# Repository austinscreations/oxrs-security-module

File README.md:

# oxrs-security-module
module 8 port pcb that allows for EOL monitoring of security sensors

2023-10-25 version 210 was created to fix p fet issue also updated JLCPCB PCBa files for the modular I2CRJ45 and port PWR extention

this baord is a 4 layer board

port PWR is 2 layers

port PWR extention is a remote switch that allows you to turn ports on and off. the use of a 1.25mm jst cable could eb used instead, simply with pin 5 being GND connect the others to this and a port will be ON

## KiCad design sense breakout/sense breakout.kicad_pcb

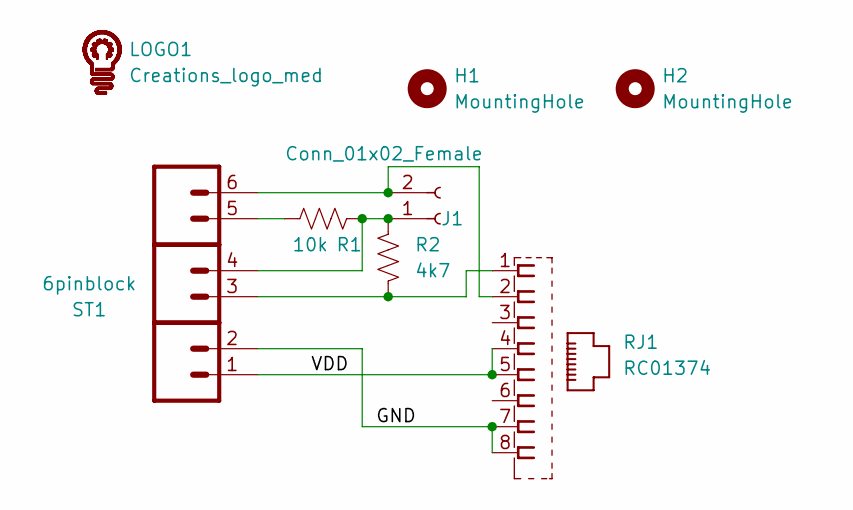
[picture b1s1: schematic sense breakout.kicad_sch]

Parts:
H1, H2: MountingHole; MountingHole_3.2mm_M3
J1: Conn_01x02_Female; PinHeader_1x02_P2.54mm_Vertical; LCSC C2829889
LOGO1: Creations_logo_med; Creations logo med
R1: 10k; R_0603_1608Metric; LCSC C25804
R2: 4k7; R_0603_1608Metric; LCSC C23162
RJ1: RC01374; LCSC C385834
ST1: 6pinblock; LCSC C192781

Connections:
/GND: RJ1.7, RJ1.8, ST1.2
/VDD: RJ1.4, RJ1.5, ST1.1
unnamed: J1.1, R1.1, R2.1, ST1.4
unnamed: J1.2, RJ1.2, ST1.6
unnamed: R1.2, ST1.5
unnamed: R2.2, RJ1.1, ST1.3

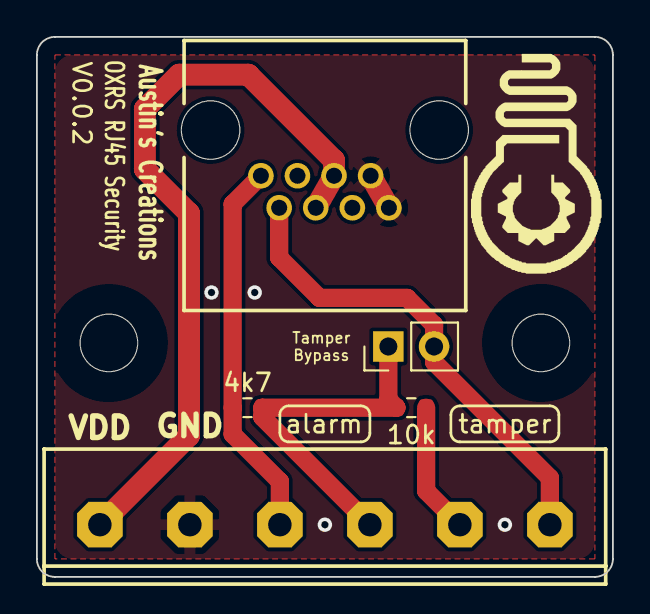
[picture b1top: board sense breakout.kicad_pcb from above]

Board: 2 copper layers, 32.0 x 30.0 mm, 8 parts (0 on the bottom side), 6 nets.

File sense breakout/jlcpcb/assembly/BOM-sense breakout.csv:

Comment,Designator,Footprint,LCSC
6pinblock,ST1,6pinblock,C192781
4k7,R2,R_0603_1608Metric,C23162
10k,R1,R_0603_1608Metric,C25804
Conn_01x02_Female,J1,PinHeader_1x02_P2.54mm_Vertical,C2829889
RC01374,RJ1,RC01374,C385834

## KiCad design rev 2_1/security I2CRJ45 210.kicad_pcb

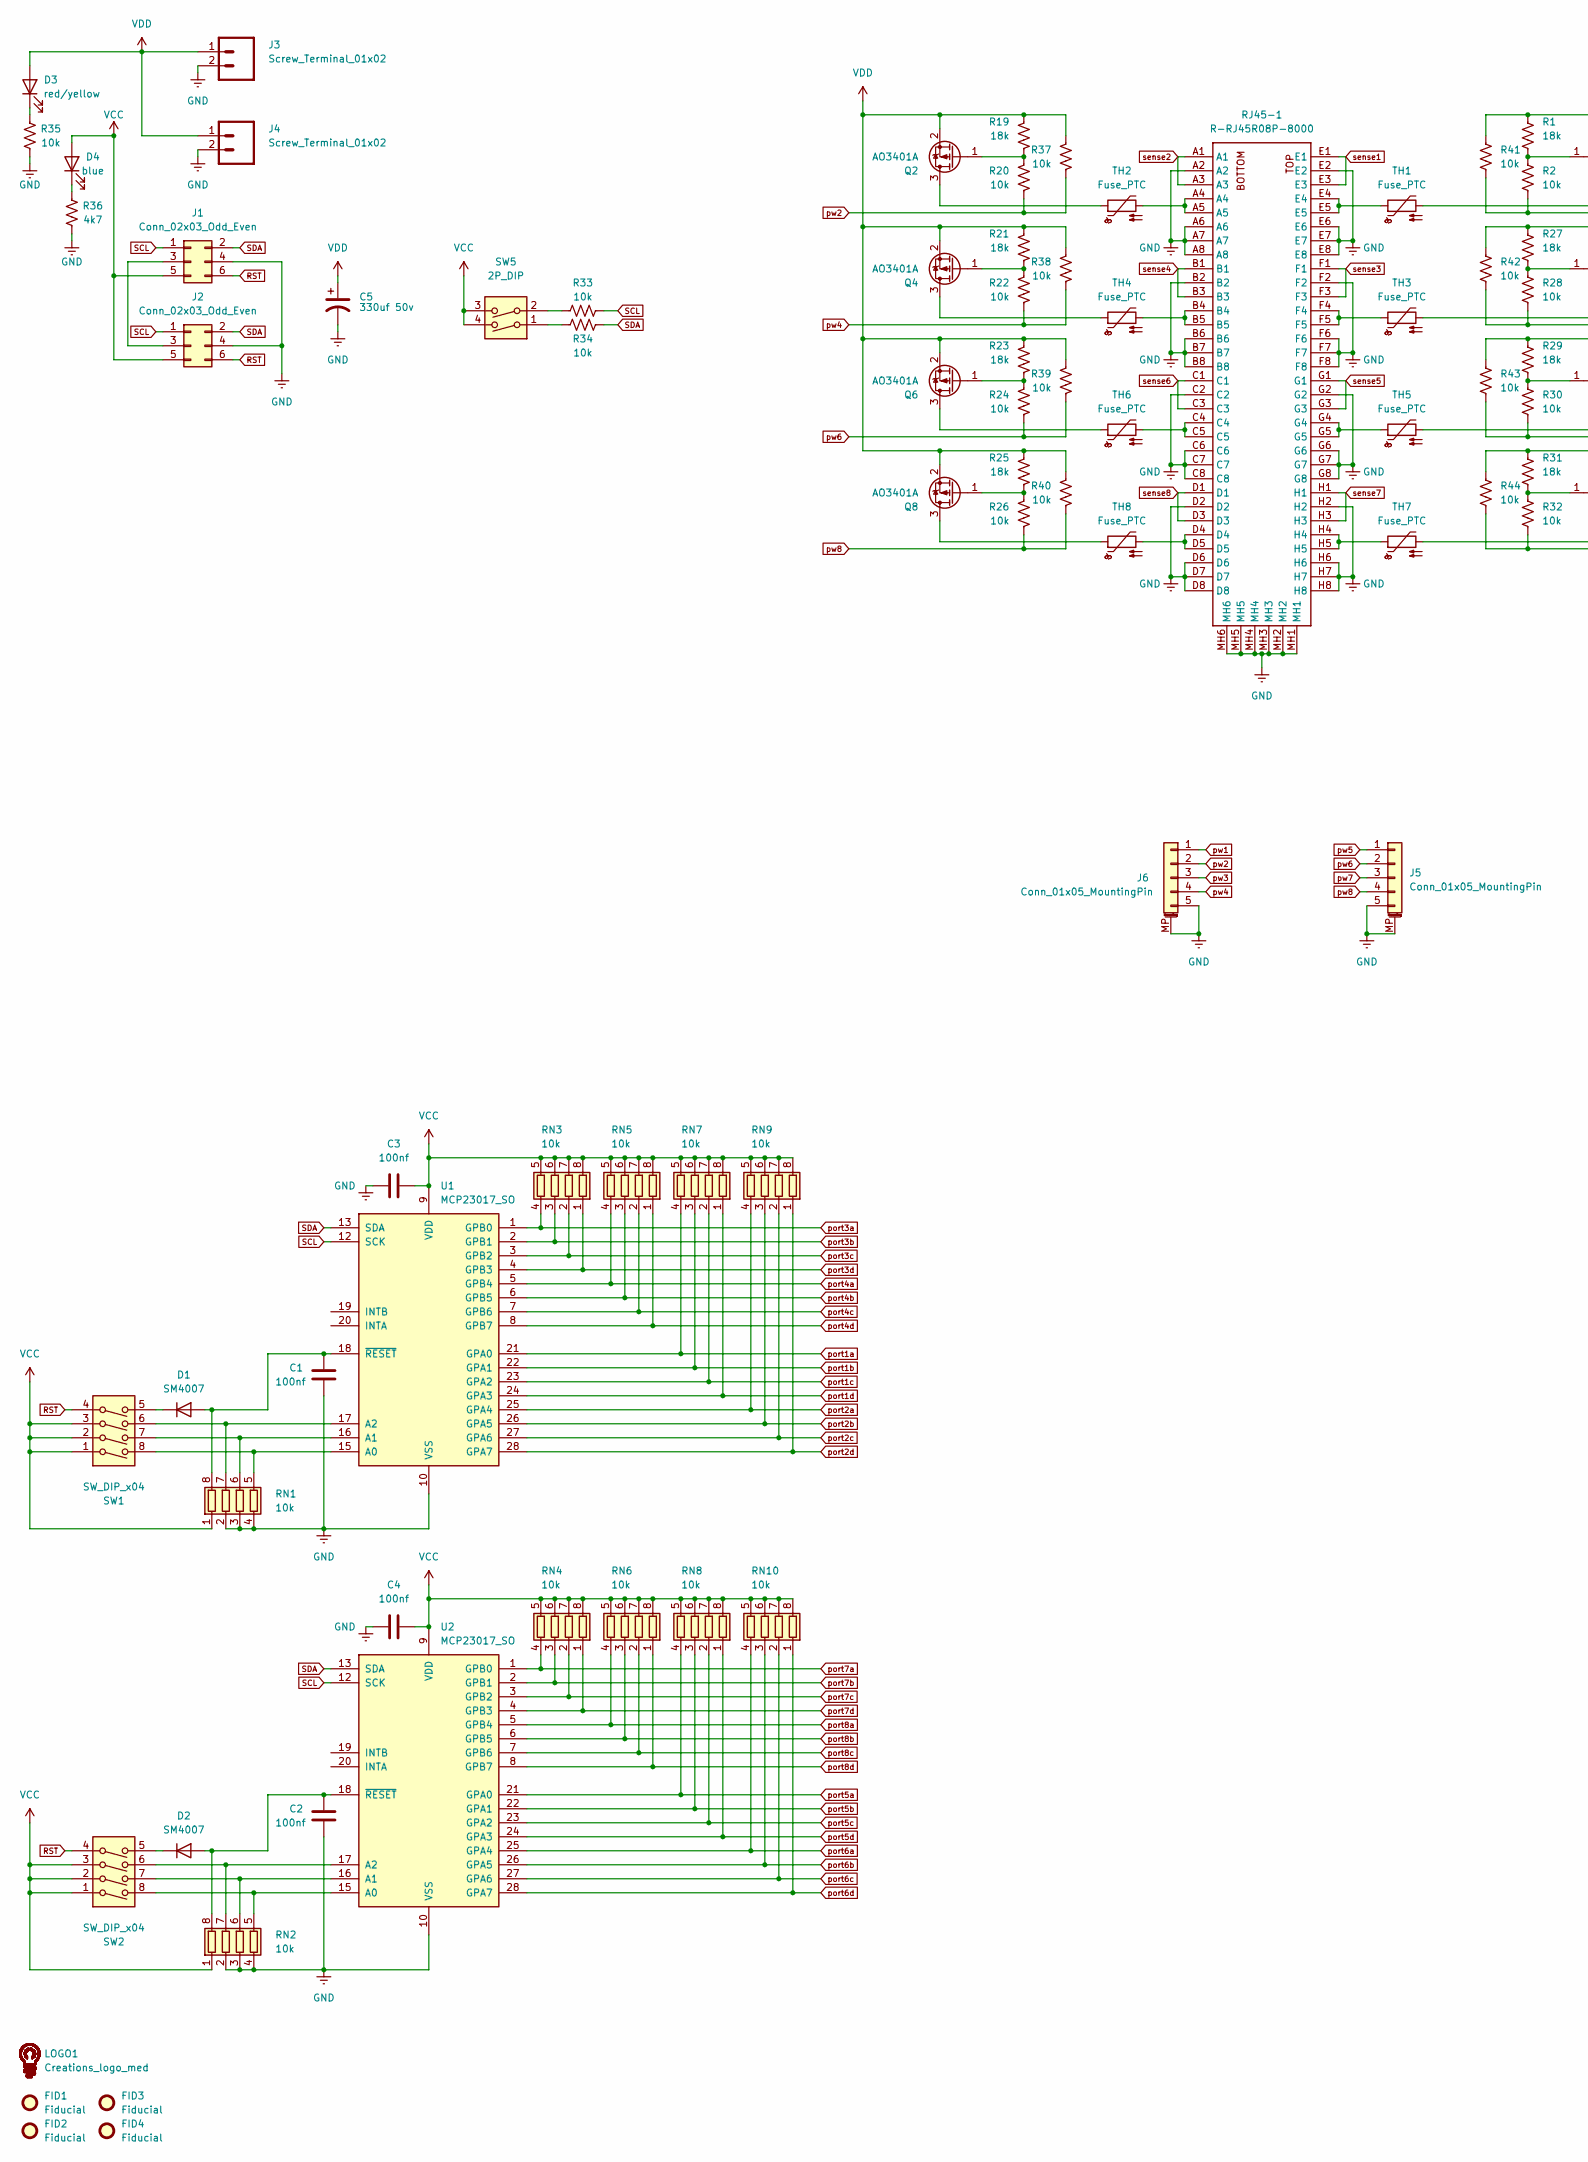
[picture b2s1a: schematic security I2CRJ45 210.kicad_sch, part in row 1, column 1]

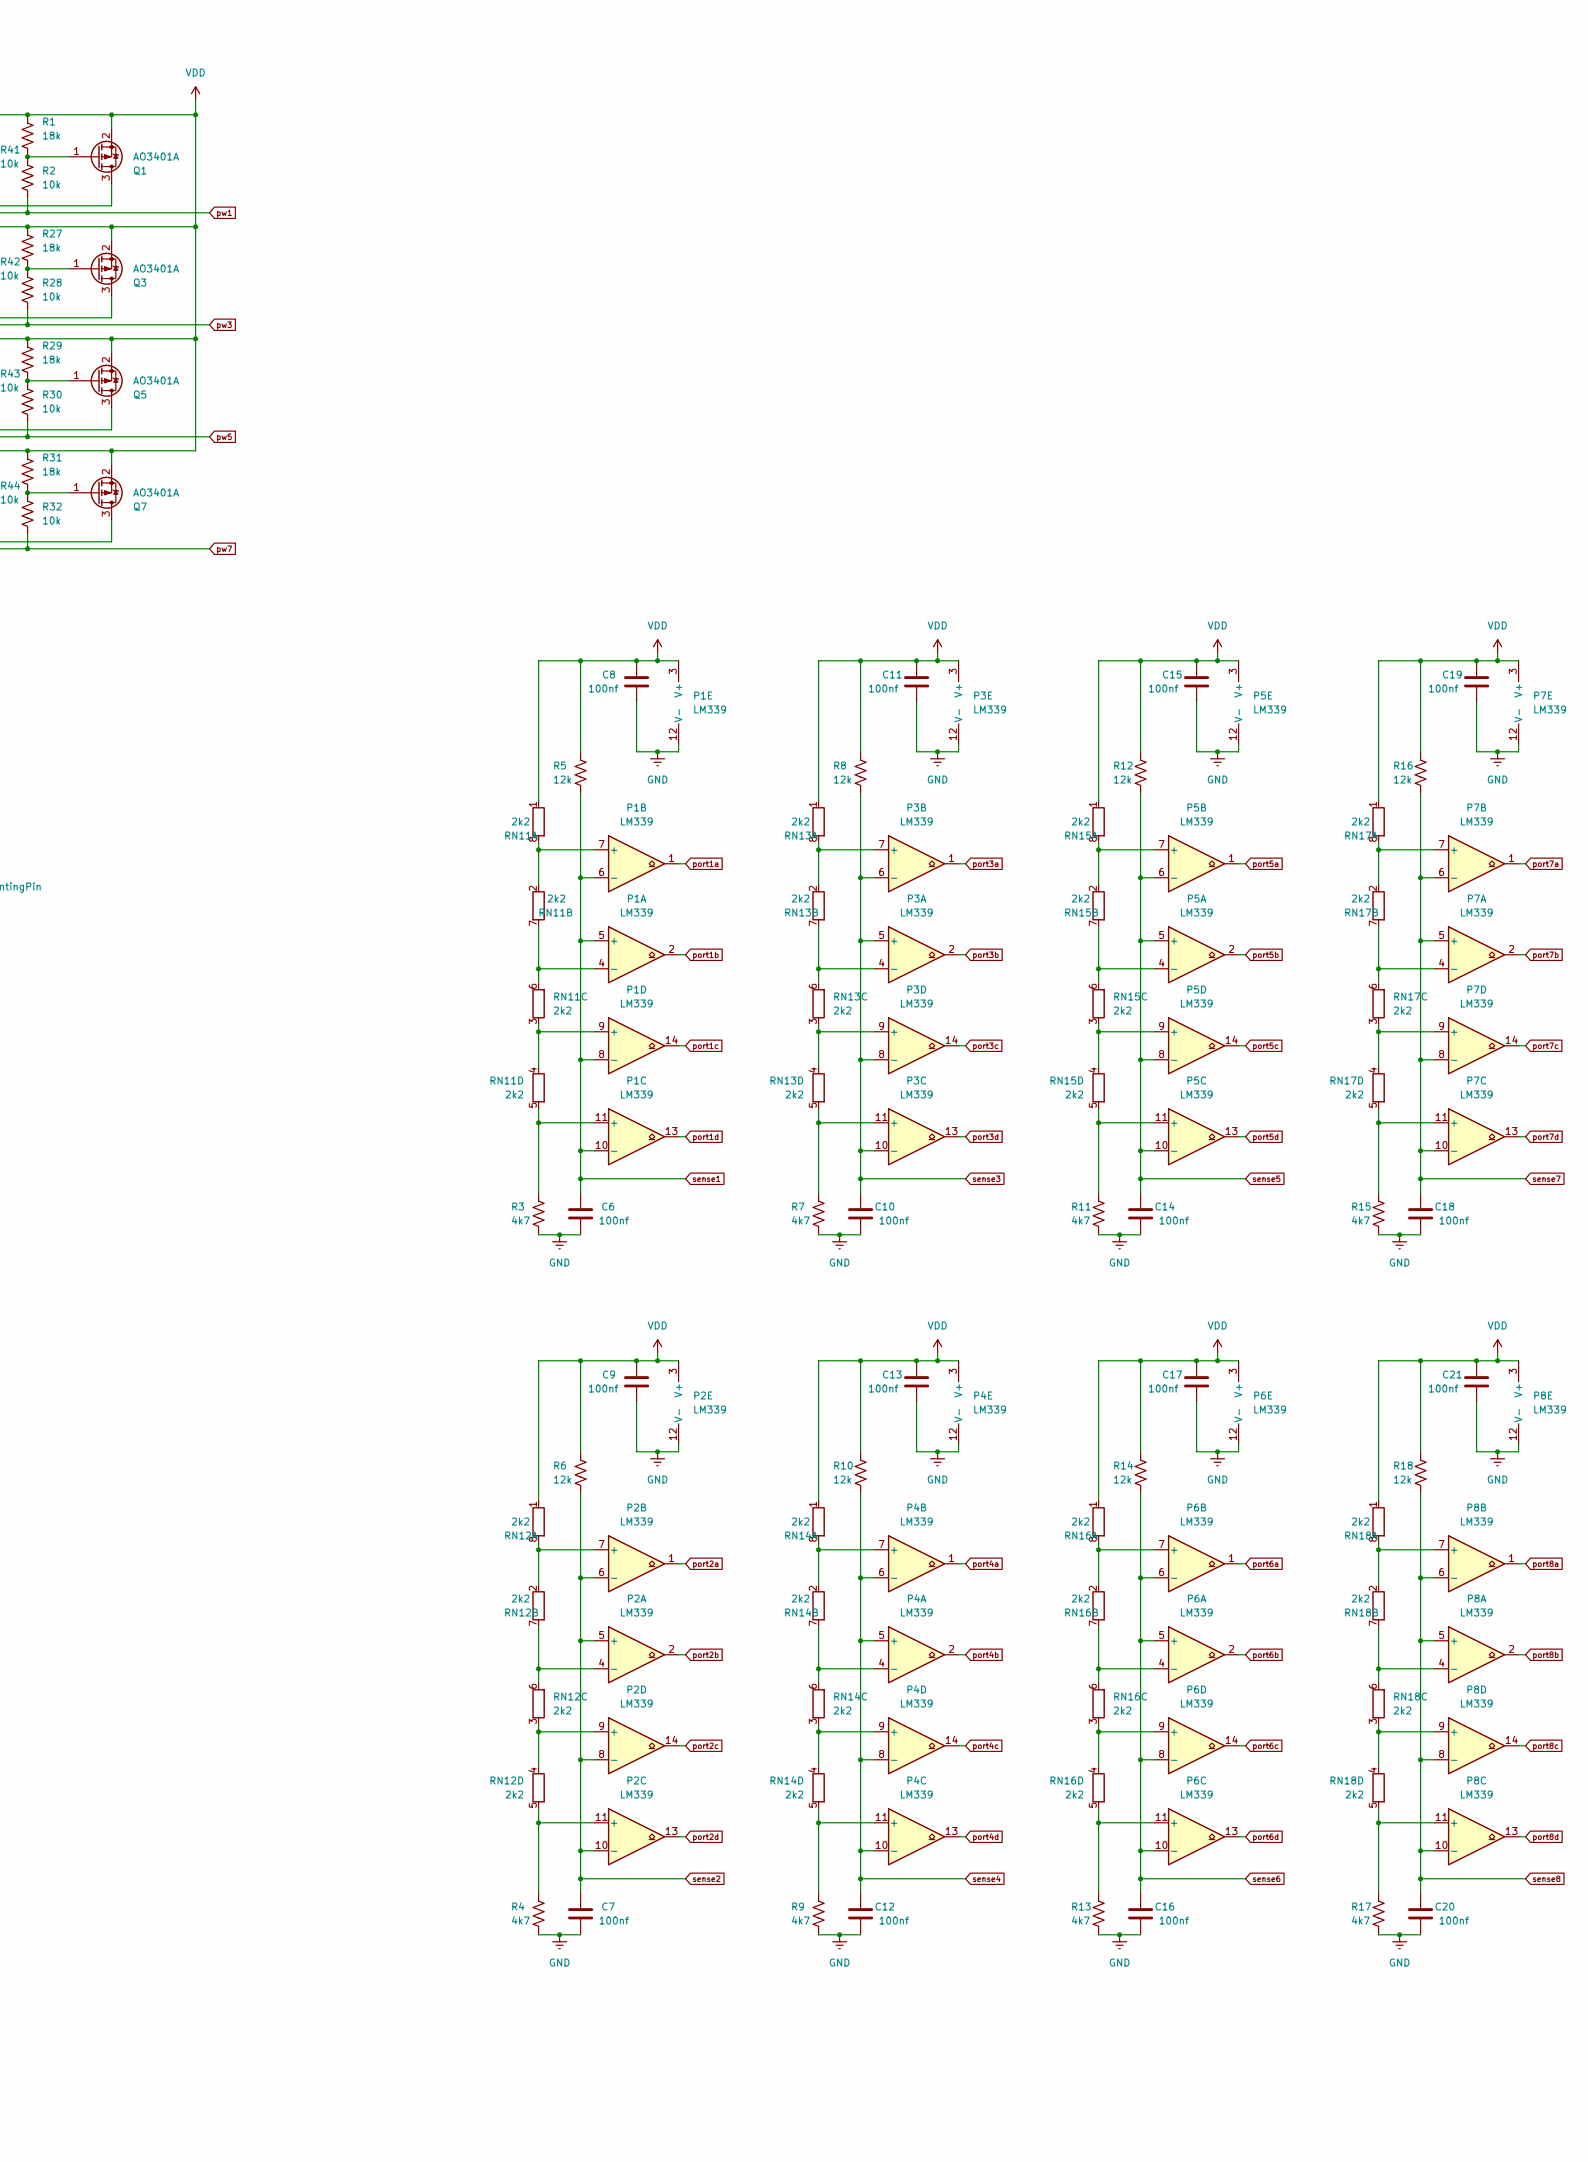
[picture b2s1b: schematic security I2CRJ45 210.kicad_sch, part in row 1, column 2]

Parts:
C1, C2, C3, C4, C6, C7, C8, C9, C10, C11, C12, C13, C14, C15, C16, C17, C18, C19, C20, C21: 100nf; C_0603_1608Metric; LCSC C14663
C5: 330uf 50v; CP_Elec_10x10; LCSC C2895745
D1, D2: SM4007; D_SOD-123F; LCSC C64898
D3: red/yellow; LED_0603_1608Metric; LCSC C72038
D4: blue; LED_0603_1608Metric; LCSC C72041
FID1, FID2, FID3, FID4: Fiducial; Fiducial_1mm_Mask2mm
J1, J2: Conn_02x03_Odd_Even; IDC-Header_2x03_P2.54mm_Vertical; LCSC C132438
J3, J4: Screw_Terminal_01x02; 2pinblock; LCSC C3703
J5, J6: Conn_01x05_MountingPin; JST_GH_SM05B-GHS-TB_1x05-1MP_P1.25mm_Horizontal; LCSC C225114
LOGO1: Creations_logo_med; Creations logo med
P1, P2, P3, P4, P5, P6, P7, P8: LM339; TSSOP-14_4.4x5mm_P0.65mm; part # 511-LM339DT; LCSC C42184
Q1, Q2, Q3, Q4, Q5, Q6, Q7, Q8: AO3401A; SOT-23; LCSC C15127
R1, R19, R21, R23, R25, R27, R29, R31: 18k; R_0603_1608Metric; LCSC C25810
R2, R20, R22, R24, R26, R28, R30, R32, R33, R34, R35, R37, R38, R39, R40, R41, R42, R43, R44: 10k; R_0603_1608Metric; LCSC C25804
R3, R4, R7, R9, R11, R13, R15, R17, R36: 4k7; R_0603_1608Metric; LCSC C21190
R5, R6, R8, R10, R12, R14, R16, R18: 12k; R_0603_1608Metric; LCSC C22790
RJ45-1: R-RJ45R08P-8000; LCSC C386760
RN1, RN2, RN3, RN4, RN5, RN6, RN7, RN8, RN9, RN10: 10k; R_Array_Convex_4x0603; LCSC C29718
RN11, RN12, RN13, RN14, RN15, RN16, RN17, RN18: 2k2; R_Array_Convex_4x0603; LCSC C12001
SW1, SW2: SW_DIP_x04; 4P_DIP; LCSC C2758183
SW5: 2P_DIP; LCSC C2758181
TH1, TH2, TH3, TH4, TH5, TH6, TH7, TH8: Fuse_PTC; R_0603_1608Metric; LCSC C883087
U1, U2: MCP23017_SO; SOIC-28W_7.5x17.9mm_P1.27mm; LCSC C47023

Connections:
GNDREF: C1.2, C2.2, C3.1, C4.1, C5.2, C6.2, C7.2, C8.2, C9.2, C10.2, C11.2, C12.2, C13.2, C14.2, C15.2, C16.2, C17.2, C18.2, C19.2, C20.2, C21.2, J1.4, J2.4, J3.2, J4.2, J5.5, J5.MP (MountPin), J6.5, J6.MP (MountPin), P1.12 (V-), P2.12 (V-), P3.12 (V-), P4.12 (V-), P5.12 (V-), P6.12 (V-), P7.12 (V-), P8.12 (V-), R3.2, R4.2, R7.2, R9.2, R11.2, R13.2, R15.2, R17.2, R35.2, R36.2, RJ45-1.A2, RJ45-1.A6, RJ45-1.A7, RJ45-1.A8, RJ45-1.B2, RJ45-1.B6, RJ45-1.B7, RJ45-1.B8, RJ45-1.C2, RJ45-1.C6, RJ45-1.C7, RJ45-1.C8, RJ45-1.D2, RJ45-1.D6, RJ45-1.D7, RJ45-1.D8, RJ45-1.E2, RJ45-1.E6, RJ45-1.E7, RJ45-1.E8, RJ45-1.F2, RJ45-1.F6, RJ45-1.F7, RJ45-1.F8, RJ45-1.G2, RJ45-1.G6, RJ45-1.G7, RJ45-1.G8, RJ45-1.H2, RJ45-1.H6, RJ45-1.H7, RJ45-1.H8, RJ45-1.MH1, RJ45-1.MH2, RJ45-1.MH3, RJ45-1.MH4, RJ45-1.MH5, RJ45-1.MH6, RN1.2 (R2.1), RN1.3 (R3.1), RN1.4 (R4.1), RN2.2 (R2.1), RN2.3 (R3.1), RN2.4 (R4.1), U1.10 (VSS), U2.10 (VSS)
unnamed: C1.1, D1.2 (A), RN1.8 (R1.2), U1.18 (~RESET)
unnamed: C2.1, D2.2 (A), RN2.8 (R1.2), U2.18 (~RESET)
unnamed: D1.1 (K), SW1.5
unnamed: D2.1 (K), SW2.5
unnamed: D3.1 (K), R35.1
unnamed: D4.1 (K), R36.1
unnamed: J1.3, J2.3
unnamed: P1.4 (-), RN11.6 (R3.2), RN11.7 (R2.2)
unnamed: P1.7 (+), RN11.2 (R2.1), RN11.8 (R1.2)
unnamed: P1.9 (+), RN11.3 (R3.1), RN11.4 (R4.1)
unnamed: P1.11 (+), R3.1, RN11.5 (R4.2)
unnamed: P2.4 (-), RN12.6 (R3.2), RN12.7 (R2.2)
unnamed: P2.7 (+), RN12.2 (R2.1), RN12.8 (R1.2)
unnamed: P2.9 (+), RN12.3 (R3.1), RN12.4 (R4.1)
unnamed: P2.11 (+), R4.1, RN12.5 (R4.2)
unnamed: P3.4 (-), RN13.6 (R3.2), RN13.7 (R2.2)
unnamed: P3.7 (+), RN13.2 (R2.1), RN13.8 (R1.2)
unnamed: P3.9 (+), RN13.3 (R3.1), RN13.4 (R4.1)
unnamed: P3.11 (+), R7.1, RN13.5 (R4.2)
unnamed: P4.4 (-), RN14.6 (R3.2), RN14.7 (R2.2)
unnamed: P4.7 (+), RN14.2 (R2.1), RN14.8 (R1.2)
unnamed: P4.9 (+), RN14.3 (R3.1), RN14.4 (R4.1)
unnamed: P4.11 (+), R9.1, RN14.5 (R4.2)
unnamed: P5.4 (-), RN15.6 (R3.2), RN15.7 (R2.2)
unnamed: P5.7 (+), RN15.2 (R2.1), RN15.8 (R1.2)
unnamed: P5.9 (+), RN15.3 (R3.1), RN15.4 (R4.1)
unnamed: P5.11 (+), R11.1, RN15.5 (R4.2)
unnamed: P6.4 (-), RN16.6 (R3.2), RN16.7 (R2.2)
unnamed: P6.7 (+), RN16.2 (R2.1), RN16.8 (R1.2)
unnamed: P6.9 (+), RN16.3 (R3.1), RN16.4 (R4.1)
unnamed: P6.11 (+), R13.1, RN16.5 (R4.2)
unnamed: P7.4 (-), RN17.6 (R3.2), RN17.7 (R2.2)
unnamed: P7.7 (+), RN17.2 (R2.1), RN17.8 (R1.2)
unnamed: P7.9 (+), RN17.3 (R3.1), RN17.4 (R4.1)
unnamed: P7.11 (+), R15.1, RN17.5 (R4.2)
unnamed: P8.4 (-), RN18.6 (R3.2), RN18.7 (R2.2)
unnamed: P8.7 (+), RN18.2 (R2.1), RN18.8 (R1.2)
unnamed: P8.9 (+), RN18.3 (R3.1), RN18.4 (R4.1)
unnamed: P8.11 (+), R17.1, RN18.5 (R4.2)
unnamed: Q1.1 (G), R1.2, R2.1
unnamed: Q1.3 (D), TH1.2
unnamed: Q2.1 (G), R19.2, R20.1
unnamed: Q2.3 (D), TH2.1
unnamed: Q3.1 (G), R27.2, R28.1
unnamed: Q3.3 (D), TH3.2
unnamed: Q4.1 (G), R21.2, R22.1
unnamed: Q4.3 (D), TH4.1
unnamed: Q5.1 (G), R29.2, R30.1
unnamed: Q5.3 (D), TH5.2
unnamed: Q6.1 (G), R23.2, R24.1
unnamed: Q6.3 (D), TH6.1
unnamed: Q7.1 (G), R31.2, R32.1
unnamed: Q7.3 (D), TH7.2
unnamed: Q8.1 (G), R25.2, R26.1
unnamed: Q8.3 (D), TH8.1
unnamed: R33.1, SW5.2
unnamed: R34.1, SW5.1
unnamed: RJ45-1.A4, RJ45-1.A5, TH2.2
unnamed: RJ45-1.B4, RJ45-1.B5, TH4.2
unnamed: RJ45-1.C4, RJ45-1.C5, TH6.2
unnamed: RJ45-1.D4, RJ45-1.D5, TH8.2
unnamed: RJ45-1.E4, RJ45-1.E5, TH1.1
unnamed: RJ45-1.F4, RJ45-1.F5, TH3.1
unnamed: RJ45-1.G4, RJ45-1.G5, TH5.1
unnamed: RJ45-1.H4, RJ45-1.H5, TH7.1
unnamed: RN1.5 (R4.2), SW1.8, U1.15 (A0)
unnamed: RN1.6 (R3.2), SW1.7, U1.16 (A1)
unnamed: RN1.7 (R2.2), SW1.6, U1.17 (A2)
unnamed: RN2.5 (R4.2), SW2.8, U2.15 (A0)
unnamed: RN2.6 (R3.2), SW2.7, U2.16 (A1)
unnamed: RN2.7 (R2.2), SW2.6, U2.17 (A2)
RST: J1.6, J2.6, SW1.4, SW2.4
SCL: J1.1, J2.1, R33.2, U1.12 (SCK), U2.12 (SCK)
SDA: J1.2, J2.2, R34.2, U1.13 (SDA), U2.13 (SDA)
VCC: C3.2, C4.2, D4.2 (A), J1.5, J2.5, RN1.1 (R1.1), RN2.1 (R1.1), RN3.5 (R4.2), RN3.6 (R3.2), RN3.7 (R2.2), RN3.8 (R1.2), RN4.5 (R4.2), RN4.6 (R3.2), RN4.7 (R2.2), RN4.8 (R1.2), RN5.5 (R4.2), RN5.6 (R3.2), RN5.7 (R2.2), RN5.8 (R1.2), RN6.5 (R4.2), RN6.6 (R3.2), RN6.7 (R2.2), RN6.8 (R1.2), RN7.5 (R4.2), RN7.6 (R3.2), RN7.7 (R2.2), RN7.8 (R1.2), RN8.5 (R4.2), RN8.6 (R3.2), RN8.7 (R2.2), RN8.8 (R1.2), RN9.5 (R4.2), RN9.6 (R3.2), RN9.7 (R2.2), RN9.8 (R1.2), RN10.5 (R4.2), RN10.6 (R3.2), RN10.7 (R2.2), RN10.8 (R1.2), SW1.1, SW1.2, SW1.3, SW2.1, SW2.2, SW2.3, SW5.3, SW5.4, U1.9 (VDD), U2.9 (VDD)
VDD: C5.1, C8.1, C9.1, C11.1, C13.1, C15.1, C17.1, C19.1, C21.1, D3.2 (A), J3.1, J4.1, P1.3 (V+), P2.3 (V+), P3.3 (V+), P4.3 (V+), P5.3 (V+), P6.3 (V+), P7.3 (V+), P8.3 (V+), Q1.2 (S), Q2.2 (S), Q3.2 (S), Q4.2 (S), Q5.2 (S), Q6.2 (S), Q7.2 (S), Q8.2 (S), R1.1, R5.1, R6.1, R8.1, R10.1, R12.1, R14.1, R16.1, R18.1, R19.1, R21.1, R23.1, R25.1, R27.1, R29.1, R31.1, R37.1, R38.1, R39.1, R40.1, R41.1, R42.1, R43.1, R44.1, RN11.1 (R1.1), RN12.1 (R1.1), RN13.1 (R1.1), RN14.1 (R1.1), RN15.1 (R1.1), RN16.1 (R1.1), RN17.1 (R1.1), RN18.1 (R1.1)
port1a: P1.1, RN7.4 (R4.1), U1.21 (GPA0)
port1b: P1.2, RN7.3 (R3.1), U1.22 (GPA1)
port1c: P1.14, RN7.2 (R2.1), U1.23 (GPA2)
port1d: P1.13, RN7.1 (R1.1), U1.24 (GPA3)
port2a: P2.1, RN9.4 (R4.1), U1.25 (GPA4)
port2b: P2.2, RN9.3 (R3.1), U1.26 (GPA5)
port2c: P2.14, RN9.2 (R2.1), U1.27 (GPA6)
port2d: P2.13, RN9.1 (R1.1), U1.28 (GPA7)
port3a: P3.1, RN3.4 (R4.1), U1.1 (GPB0)
port3b: P3.2, RN3.3 (R3.1), U1.2 (GPB1)
port3c: P3.14, RN3.2 (R2.1), U1.3 (GPB2)
port3d: P3.13, RN3.1 (R1.1), U1.4 (GPB3)
port4a: P4.1, RN5.4 (R4.1), U1.5 (GPB4)
port4b: P4.2, RN5.3 (R3.1), U1.6 (GPB5)
port4c: P4.14, RN5.2 (R2.1), U1.7 (GPB6)
port4d: P4.13, RN5.1 (R1.1), U1.8 (GPB7)
port5a: P5.1, RN8.4 (R4.1), U2.21 (GPA0)
port5b: P5.2, RN8.3 (R3.1), U2.22 (GPA1)
port5c: P5.14, RN8.2 (R2.1), U2.23 (GPA2)
port5d: P5.13, RN8.1 (R1.1), U2.24 (GPA3)
port6a: P6.1, RN10.4 (R4.1), U2.25 (GPA4)
port6b: P6.2, RN10.3 (R3.1), U2.26 (GPA5)
port6c: P6.14, RN10.2 (R2.1), U2.27 (GPA6)
port6d: P6.13, RN10.1 (R1.1), U2.28 (GPA7)
port7a: P7.1, RN4.4 (R4.1), U2.1 (GPB0)
port7b: P7.2, RN4.3 (R3.1), U2.2 (GPB1)
port7c: P7.14, RN4.2 (R2.1), U2.3 (GPB2)
port7d: P7.13, RN4.1 (R1.1), U2.4 (GPB3)
port8a: P8.1, RN6.4 (R4.1), U2.5 (GPB4)
port8b: P8.2, RN6.3 (R3.1), U2.6 (GPB5)
port8c: P8.14, RN6.2 (R2.1), U2.7 (GPB6)
port8d: P8.13, RN6.1 (R1.1), U2.8 (GPB7)
pw1: J6.1, R2.2, R41.2
pw2: J6.2, R20.2, R37.2
pw3: J6.3, R28.2, R42.2
pw4: J6.4, R22.2, R38.2
pw5: J5.1, R30.2, R43.2
pw6: J5.2, R24.2, R39.2
pw7: J5.3, R32.2, R44.2
pw8: J5.4, R26.2, R40.2
sense1: C6.1, P1.5 (+), P1.6 (-), P1.8 (-), P1.10 (-), R5.2, RJ45-1.E1, RJ45-1.E3
sense2: C7.1, P2.5 (+), P2.6 (-), P2.8 (-), P2.10 (-), R6.2, RJ45-1.A1, RJ45-1.A3
sense3: C10.1, P3.5 (+), P3.6 (-), P3.8 (-), P3.10 (-), R8.2, RJ45-1.F1, RJ45-1.F3
sense4: C12.1, P4.5 (+), P4.6 (-), P4.8 (-), P4.10 (-), R10.2, RJ45-1.B1, RJ45-1.B3
sense5: C14.1, P5.5 (+), P5.6 (-), P5.8 (-), P5.10 (-), R12.2, RJ45-1.G1, RJ45-1.G3
sense6: C16.1, P6.5 (+), P6.6 (-), P6.8 (-), P6.10 (-), R14.2, RJ45-1.C1, RJ45-1.C3
sense7: C18.1, P7.5 (+), P7.6 (-), P7.8 (-), P7.10 (-), R16.2, RJ45-1.H1, RJ45-1.H3
sense8: C20.1, P8.5 (+), P8.6 (-), P8.8 (-), P8.10 (-), R18.2, RJ45-1.D1, RJ45-1.D3

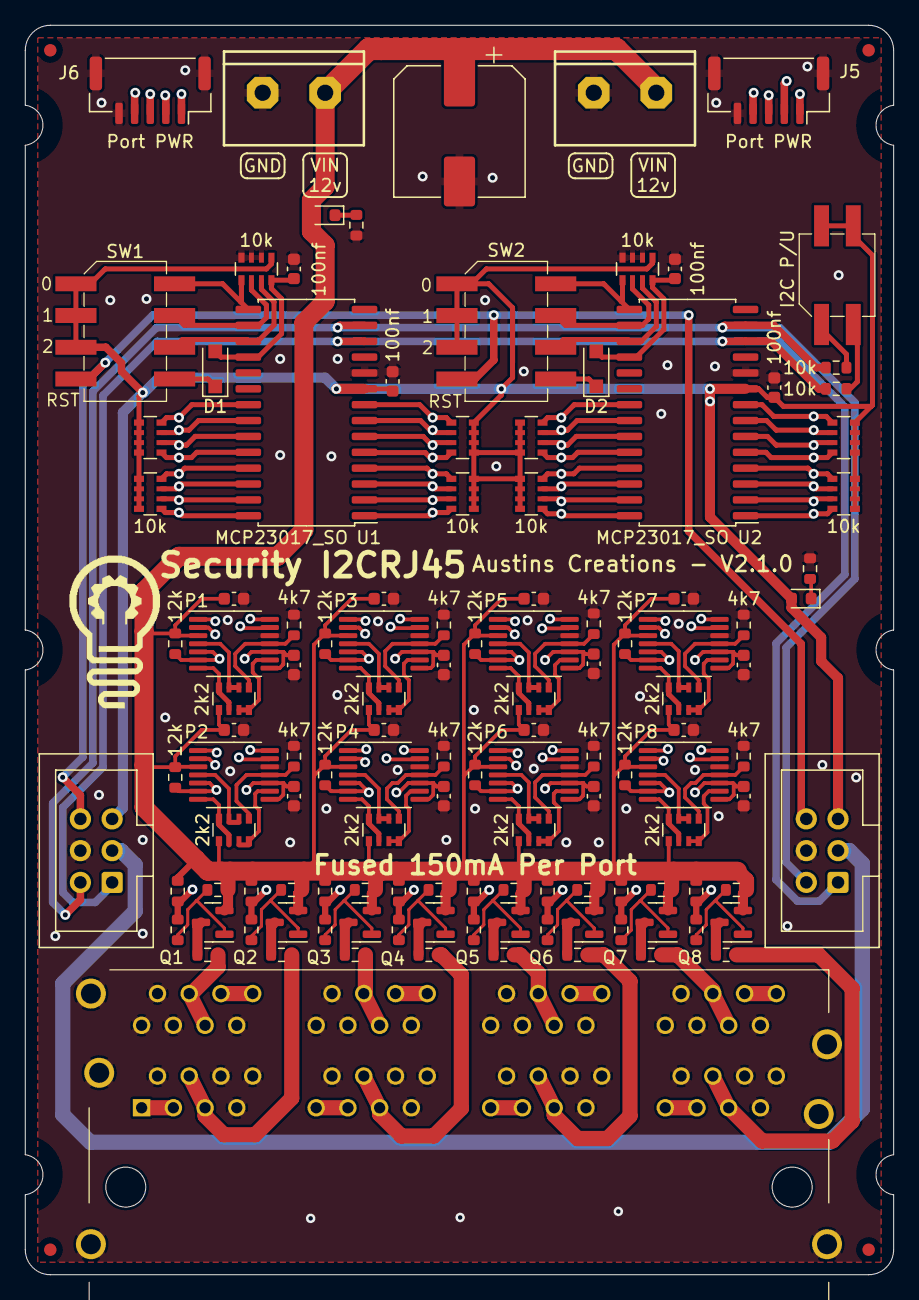
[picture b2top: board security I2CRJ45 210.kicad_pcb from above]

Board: 4 copper layers, 69.5 x 100.0 mm, 128 parts (0 on the bottom side), 125 nets.

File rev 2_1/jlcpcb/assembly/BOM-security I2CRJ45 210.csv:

Comment,Designator,Footprint,LCSC
2k2,"RN11,RN12,RN13,RN14,RN15,RN16,RN17,RN18",R_Array_Convex_4x0603,C12001
Conn_02x03_Odd_Even,"J1,J2",IDC-Header_2x03_P2.54mm_Vertical,C132438
100nf,"C1,C10,C11,C12,C13,C14,C15,C16,C17,C18,C19,C2,C20,C21,C3,C4,C6,C7,C8,C9",C_0603_1608Metric,C14663
AO3401A,"Q1,Q2,Q3,Q4,Q5,Q6,Q7,Q8",SOT-23,C15127
4k7,"R11,R13,R15,R17,R3,R36,R4,R7,R9",R_0603_1608Metric,C21190
Conn_01x05_MountingPin,"J5,J6",JST_GH_SM05B-GHS-TB_1x05-1MP_P1.25mm_Horizontal,C225114
12k,"R10,R12,R14,R16,R18,R5,R6,R8",R_0603_1608Metric,C22790
10k,"R2,R20,R22,R24,R26,R28,R30,R32,R33,R34,R35,R37,R38,R39,R40,R41,R42,R43,R44",R_0603_1608Metric,C25804 
18k,"R1,R19,R21,R23,R25,R27,R29,R31",R_0603_1608Metric,C25810
2P_DIP,SW5,2P_DIP,C2758181
SW_DIP_x04,"SW1,SW2",4P_DIP,C2758183
330uf 50v,C5,CP_Elec_10x10,C2895745
10k,"RN1,RN10,RN2,RN3,RN4,RN5,RN6,RN7,RN8,RN9",R_Array_Convex_4x0603,C29718
Screw_Terminal_01x02,"J3,J4",2pinblock,C3703
R-RJ45R08P-8000,RJ45-1,R-RJ45R08P-8000,C386760
LM339,"P1,P2,P3,P4,P5,P6,P7,P8",TSSOP-14_4.4x5mm_P0.65mm,C42184
MCP23017_SO,"U1,U2",SOIC-28W_7.5x17.9mm_P1.27mm,C47023
SM4007,"D1,D2",D_SOD-123F,C64898
red/yellow,D3,LED_0603_1608Metric,C72038
blue,D4,LED_0603_1608Metric,C72041
Fuse_PTC,"TH1,TH2,TH3,TH4,TH5,TH6,TH7,TH8",R_0603_1608Metric,C883087

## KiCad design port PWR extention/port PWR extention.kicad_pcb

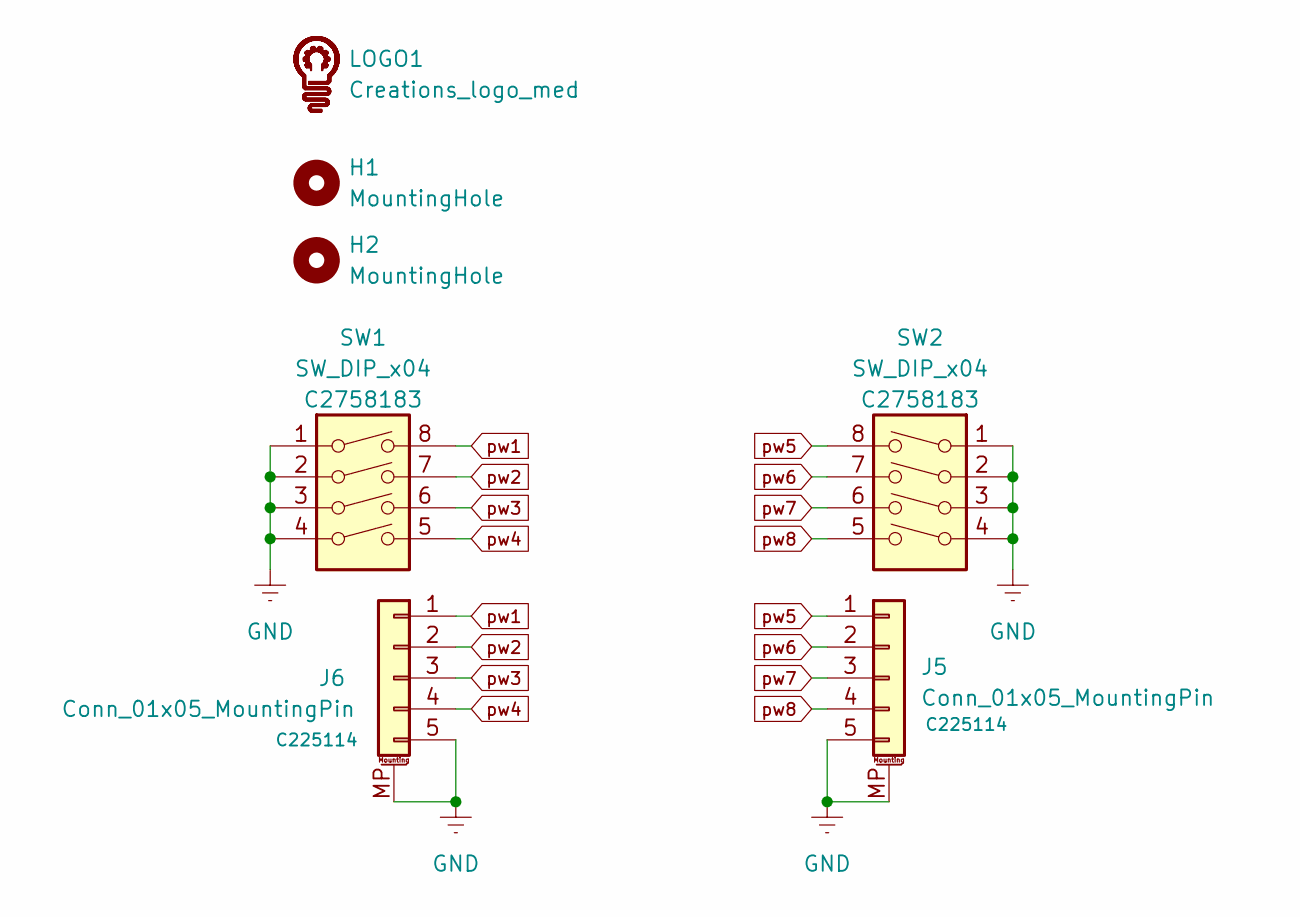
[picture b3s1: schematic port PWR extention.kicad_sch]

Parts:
H1, H2: MountingHole; MountingHole_3.2mm_M3
J5, J6: Conn_01x05_MountingPin; JST_GH_SM05B-GHS-TB_1x05-1MP_P1.25mm_Horizontal; part # C225114
LOGO1: Creations_logo_med; Creations logo med
SW1, SW2: SW_DIP_x04; 4P_DIP; part # C2758183

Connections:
GNDREF: J5.5, J5.MP (MountPin), J6.5, J6.MP (MountPin), SW1.1, SW1.2, SW1.3, SW1.4, SW2.1, SW2.2, SW2.3, SW2.4
pw1: J6.1, SW1.8
pw2: J6.2, SW1.7
pw3: J6.3, SW1.6
pw4: J6.4, SW1.5
pw5: J5.1, SW2.8
pw6: J5.2, SW2.7
pw7: J5.3, SW2.6
pw8: J5.4, SW2.5

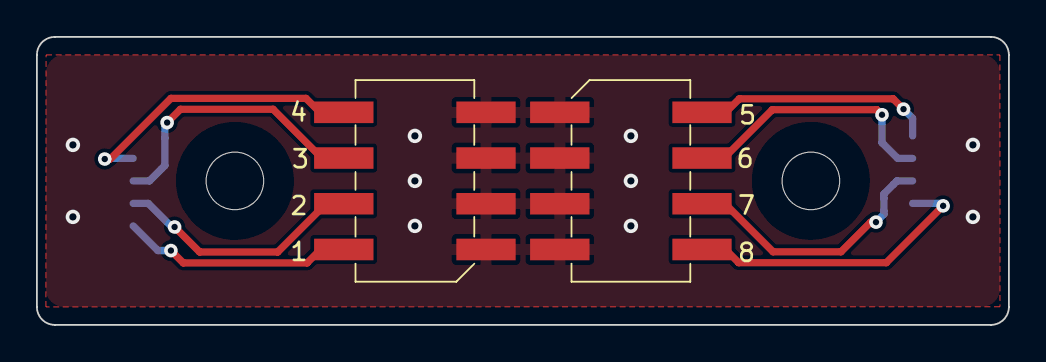
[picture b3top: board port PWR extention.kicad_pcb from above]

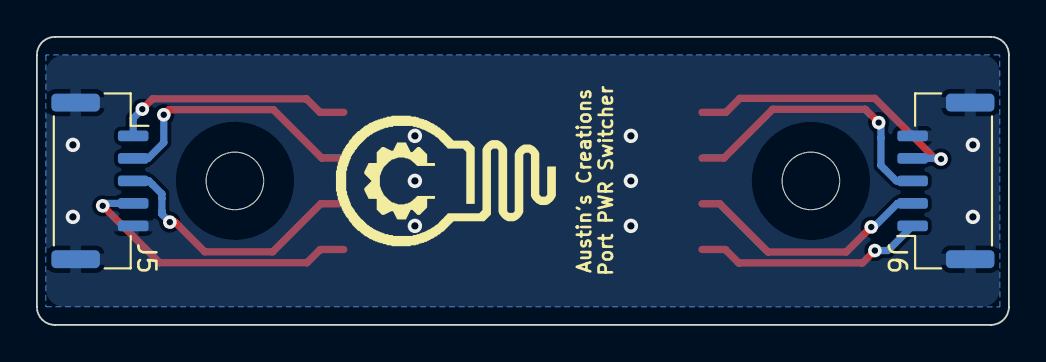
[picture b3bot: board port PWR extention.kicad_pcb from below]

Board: 2 copper layers, 54.0 x 16.0 mm, 7 parts (3 on the bottom side), 9 nets.

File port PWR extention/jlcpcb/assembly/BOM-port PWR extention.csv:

Comment,Designator,Footprint,LCSC
SW_DIP_x04,SW2,4P_DIP,
SW_DIP_x04,SW1,4P_DIP,
MountingHole,H1,MountingHole_3.2mm_M3,
MountingHole,H2,MountingHole_3.2mm_M3,
Conn_01x05_MountingPin,J6,JST_GH_SM05B-GHS-TB_1x05-1MP_P1.25mm_Horizontal,
Creations_logo_med,LOGO1,Creations logo med,
Conn_01x05_MountingPin,J5,JST_GH_SM05B-GHS-TB_1x05-1MP_P1.25mm_Horizontal,

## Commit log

2022-08-18 add photos of PCBs
2022-08-18 PCB files for security module
2022-08-18 pcb files for port power extension control
2023-05-14 Adding p fet warning
2024-08-05 update d4 led to use JLCPCB part C2286
2024-08-09 update j1 part to C492401 update rotation and position for j1
